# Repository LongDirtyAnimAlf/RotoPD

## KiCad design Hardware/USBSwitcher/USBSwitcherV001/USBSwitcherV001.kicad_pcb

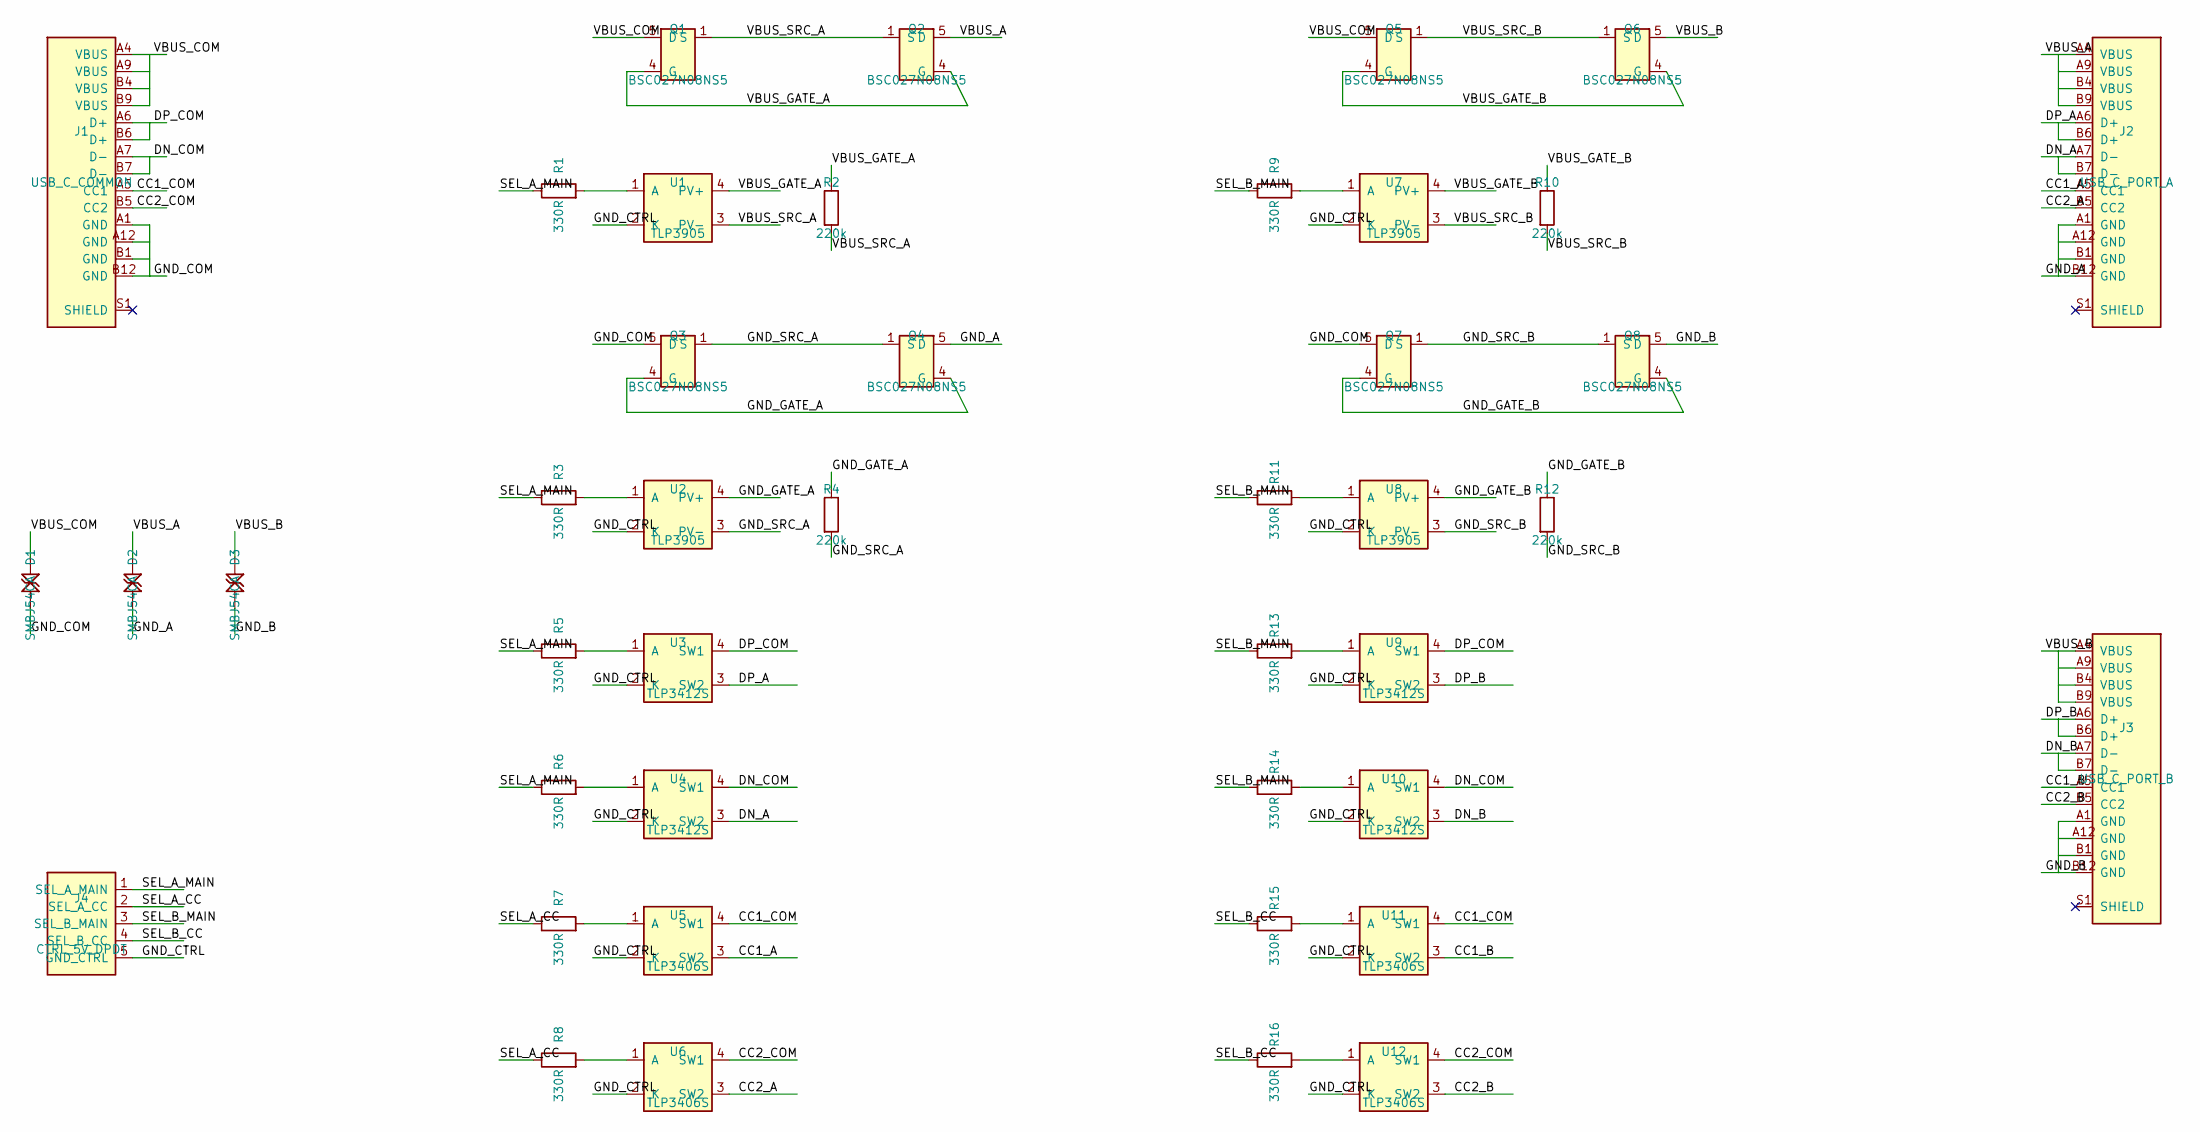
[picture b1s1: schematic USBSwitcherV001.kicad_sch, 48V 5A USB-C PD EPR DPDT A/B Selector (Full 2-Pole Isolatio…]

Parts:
D1, D2, D3: SMBJ54CA; D_SMB
J1: USB_C_COMMON; USB_C_Receptacle_GCT_USB4105-xx-A_16P_TopMnt_Horizontal
J2: USB_C_PORT_A; USB_C_Receptacle_GCT_USB4105-xx-A_16P_TopMnt_Horizontal
J3: USB_C_PORT_B; USB_C_Receptacle_GCT_USB4105-xx-A_16P_TopMnt_Horizontal
J4: CTRL_5V_DPDT; PinHeader_1x05_P2.54mm_Vertical
Q1, Q2, Q3, Q4, Q5, Q6, Q7, Q8: BSC027N08NS5; TDSON-8-1
R1, R3, R5, R6, R7, R8, R9, R11, R13, R14, R15, R16: 330R; R_0603_1608Metric
R2, R4, R10, R12: 220k; R_0603_1608Metric
U1, U2, U7, U8: TLP3905; SSOP-4_4.4x2.6mm_P1.27mm
U3, U4, U9, U10: TLP3412S; SSOP-4_4.4x2.6mm_P1.27mm
U5, U6, U11, U12: TLP3406S; SSOP-4_4.4x2.6mm_P1.27mm

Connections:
/CC1_A: J2.A5 (CC1), U5.3 (SW2)
/CC1_B: J3.A5 (CC1), U11.3 (SW2)
/CC1_COM: J1.A5 (CC1), U5.4 (SW1), U11.4 (SW1)
/CC2_A: J2.B5 (CC2), U6.3 (SW2)
/CC2_B: J3.B5 (CC2), U12.3 (SW2)
/CC2_COM: J1.B5 (CC2), U6.4 (SW1), U12.4 (SW1)
/DN_A: J2.A7 (D-), J2.B7 (D-), U4.3 (SW2)
/DN_B: J3.A7 (D-), J3.B7 (D-), U10.3 (SW2)
/DN_COM: J1.A7 (D-), J1.B7 (D-), U4.4 (SW1), U10.4 (SW1)
/DP_A: J2.A6 (D+), J2.B6 (D+), U3.3 (SW2)
/DP_B: J3.A6 (D+), J3.B6 (D+), U9.3 (SW2)
/DP_COM: J1.A6 (D+), J1.B6 (D+), U3.4 (SW1), U9.4 (SW1)
/GND_A: D2.1 (A1), J2.A1 (GND), J2.B12 (GND), Q4.5 (D)
/GND_B: D3.1 (A1), J3.A1 (GND), J3.B12 (GND), Q8.5 (D)
/GND_COM: D1.1 (A1), J1.A1 (GND), J1.B12 (GND), Q3.5 (D), Q7.5 (D)
/GND_CTRL: J4.5 (GND_CTRL), U1.2 (K), U2.2 (K), U3.2 (K), U4.2 (K), U5.2 (K), U6.2 (K), U7.2 (K), U8.2 (K), U9.2 (K), U10.2 (K), U11.2 (K), U12.2 (K)
/GND_GATE_A: Q3.4 (G), Q4.4 (G), R4.1, U2.4 (PV+)
/GND_GATE_B: Q7.4 (G), Q8.4 (G), R12.1, U8.4 (PV+)
/GND_SRC_A: Q3.1 (S), Q4.1 (S), R4.2, U2.3 (PV-)
/GND_SRC_B: Q7.1 (S), Q8.1 (S), R12.2, U8.3 (PV-)
/SEL_A_CC: J4.2 (SEL_A_CC), R7.1, R8.1
/SEL_A_MAIN: J4.1 (SEL_A_MAIN), R1.1, R3.1, R5.1, R6.1
/SEL_B_CC: J4.4 (SEL_B_CC), R15.1, R16.1
/SEL_B_MAIN: J4.3 (SEL_B_MAIN), R9.1, R11.1, R13.1, R14.1
/VBUS_A: D2.2 (A2), J2.A4 (VBUS), J2.B9 (VBUS), Q2.5 (D)
/VBUS_B: D3.2 (A2), J3.A4 (VBUS), J3.B9 (VBUS), Q6.5 (D)
/VBUS_COM: D1.2 (A2), J1.A4 (VBUS), J1.B9 (VBUS), Q1.5 (D), Q5.5 (D)
/VBUS_GATE_A: Q1.4 (G), Q2.4 (G), R2.1, U1.4 (PV+)
/VBUS_GATE_B: Q5.4 (G), Q6.4 (G), R10.1, U7.4 (PV+)
/VBUS_SRC_A: Q1.1 (S), Q2.1 (S), R2.2, U1.3 (PV-)
/VBUS_SRC_B: Q5.1 (S), Q6.1 (S), R10.2, U7.3 (PV-)
unnamed: R1.2, U1.1 (A)
unnamed: R3.2, U2.1 (A)
unnamed: R5.2, U3.1 (A)
unnamed: R6.2, U4.1 (A)
unnamed: R7.2, U5.1 (A)
unnamed: R8.2, U6.1 (A)
unnamed: R9.2, U7.1 (A)
unnamed: R11.2, U8.1 (A)
unnamed: R13.2, U9.1 (A)
unnamed: R14.2, U10.1 (A)
unnamed: R15.2, U11.1 (A)
unnamed: R16.2, U12.1 (A)

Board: 2 copper layers, 43 parts (0 on the bottom side), 43 nets, no tracks yet.

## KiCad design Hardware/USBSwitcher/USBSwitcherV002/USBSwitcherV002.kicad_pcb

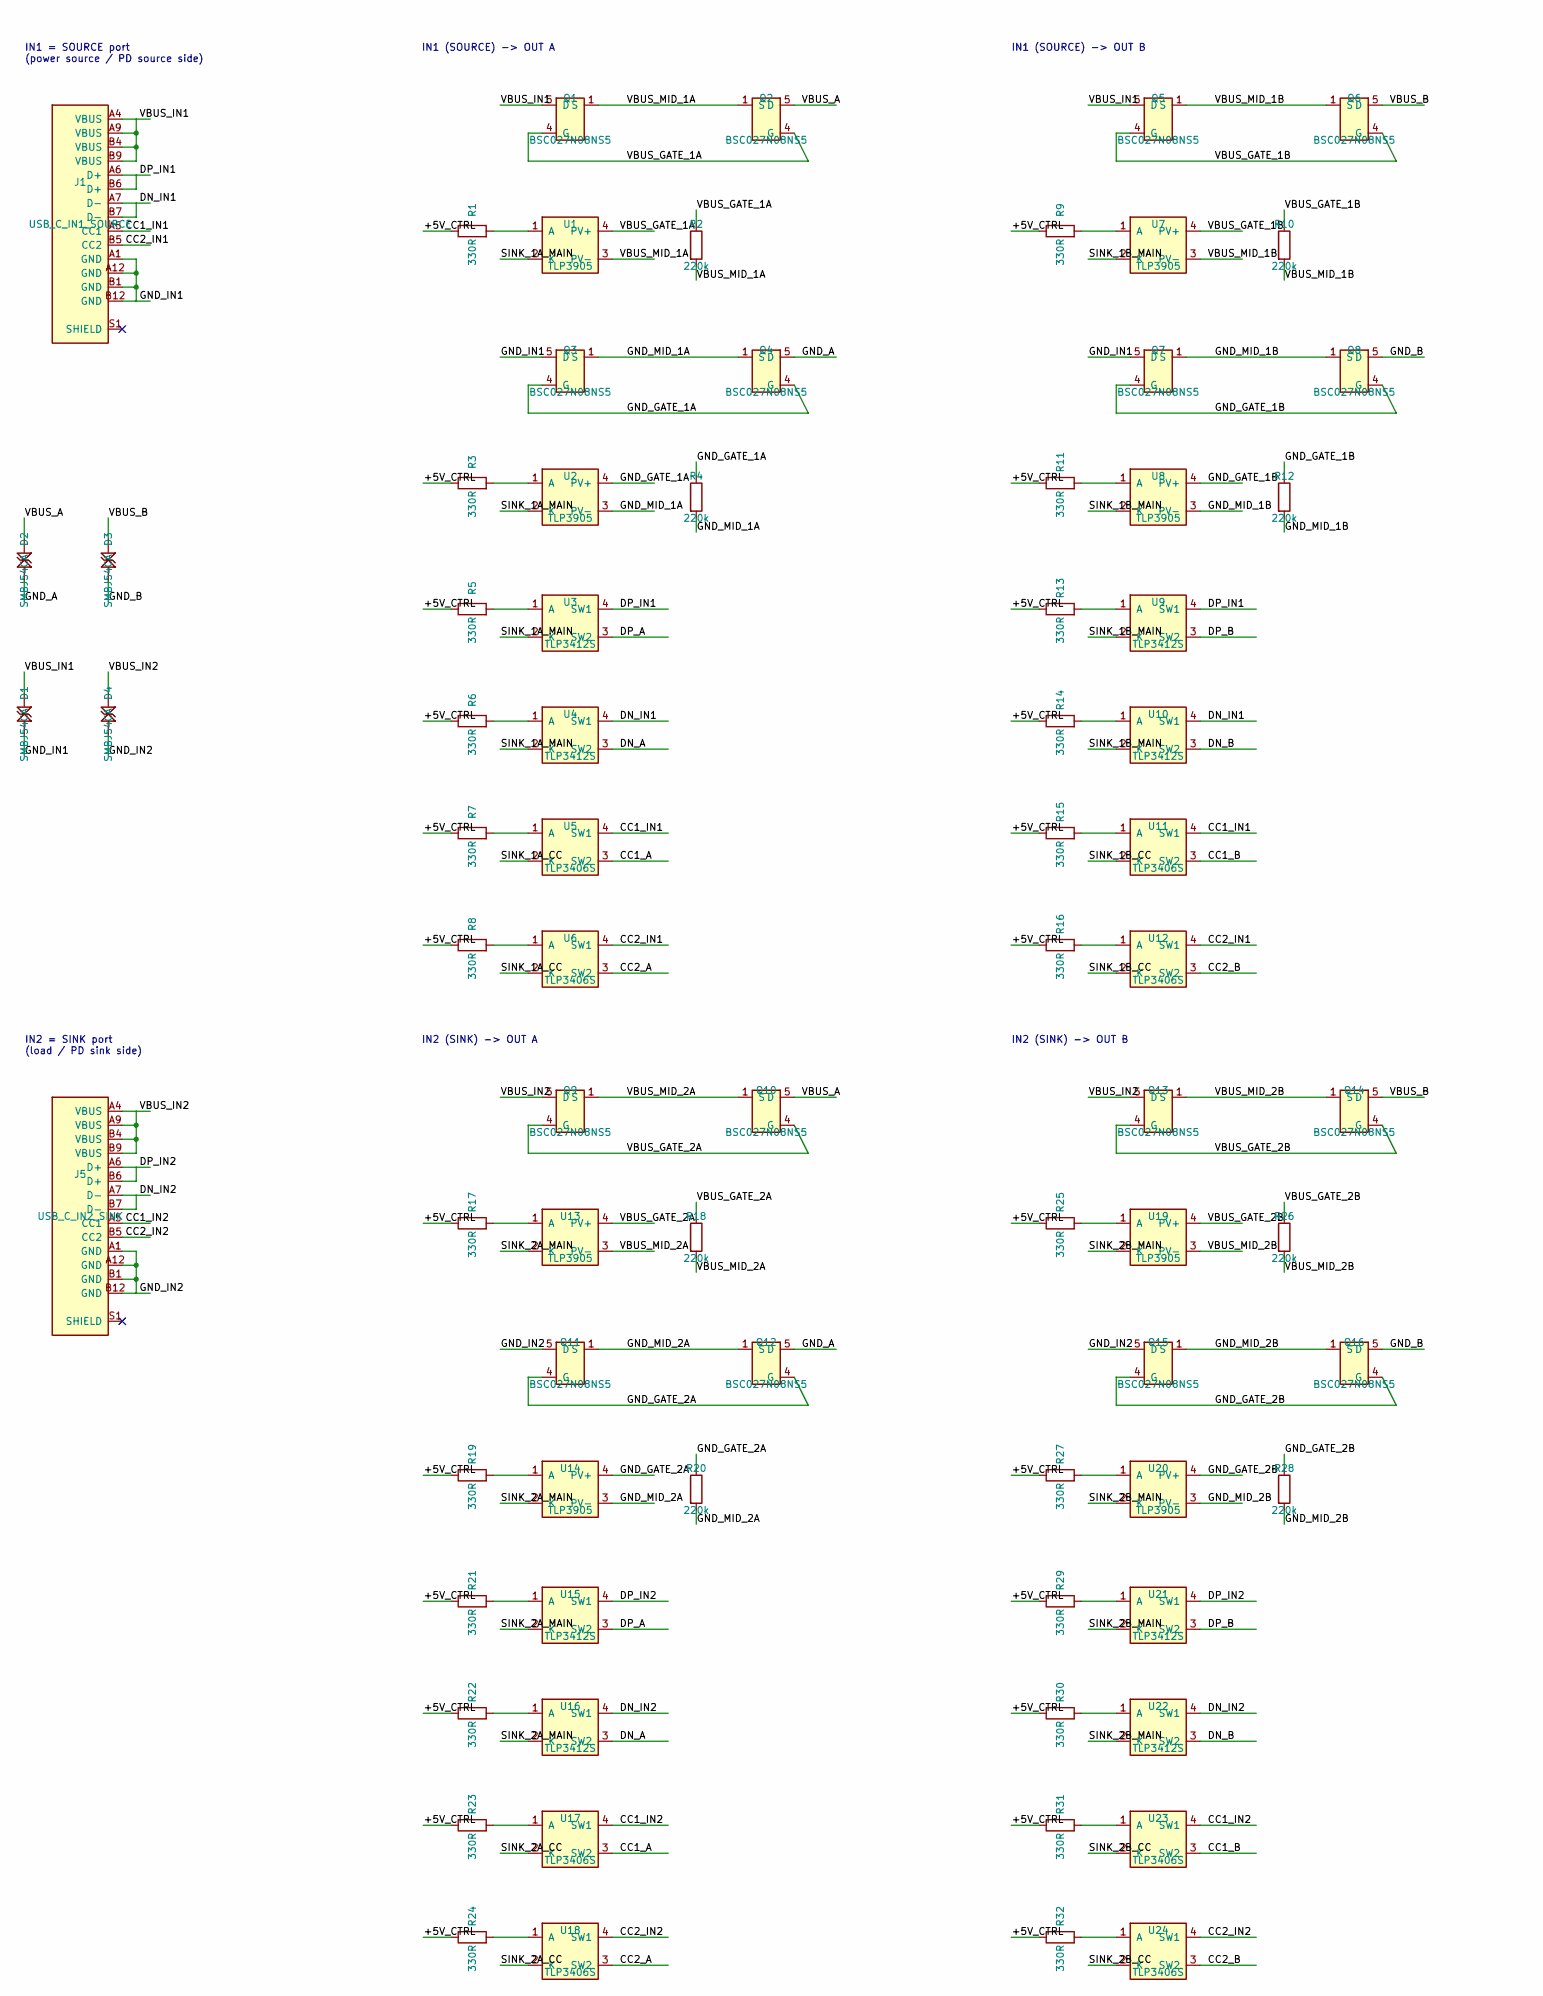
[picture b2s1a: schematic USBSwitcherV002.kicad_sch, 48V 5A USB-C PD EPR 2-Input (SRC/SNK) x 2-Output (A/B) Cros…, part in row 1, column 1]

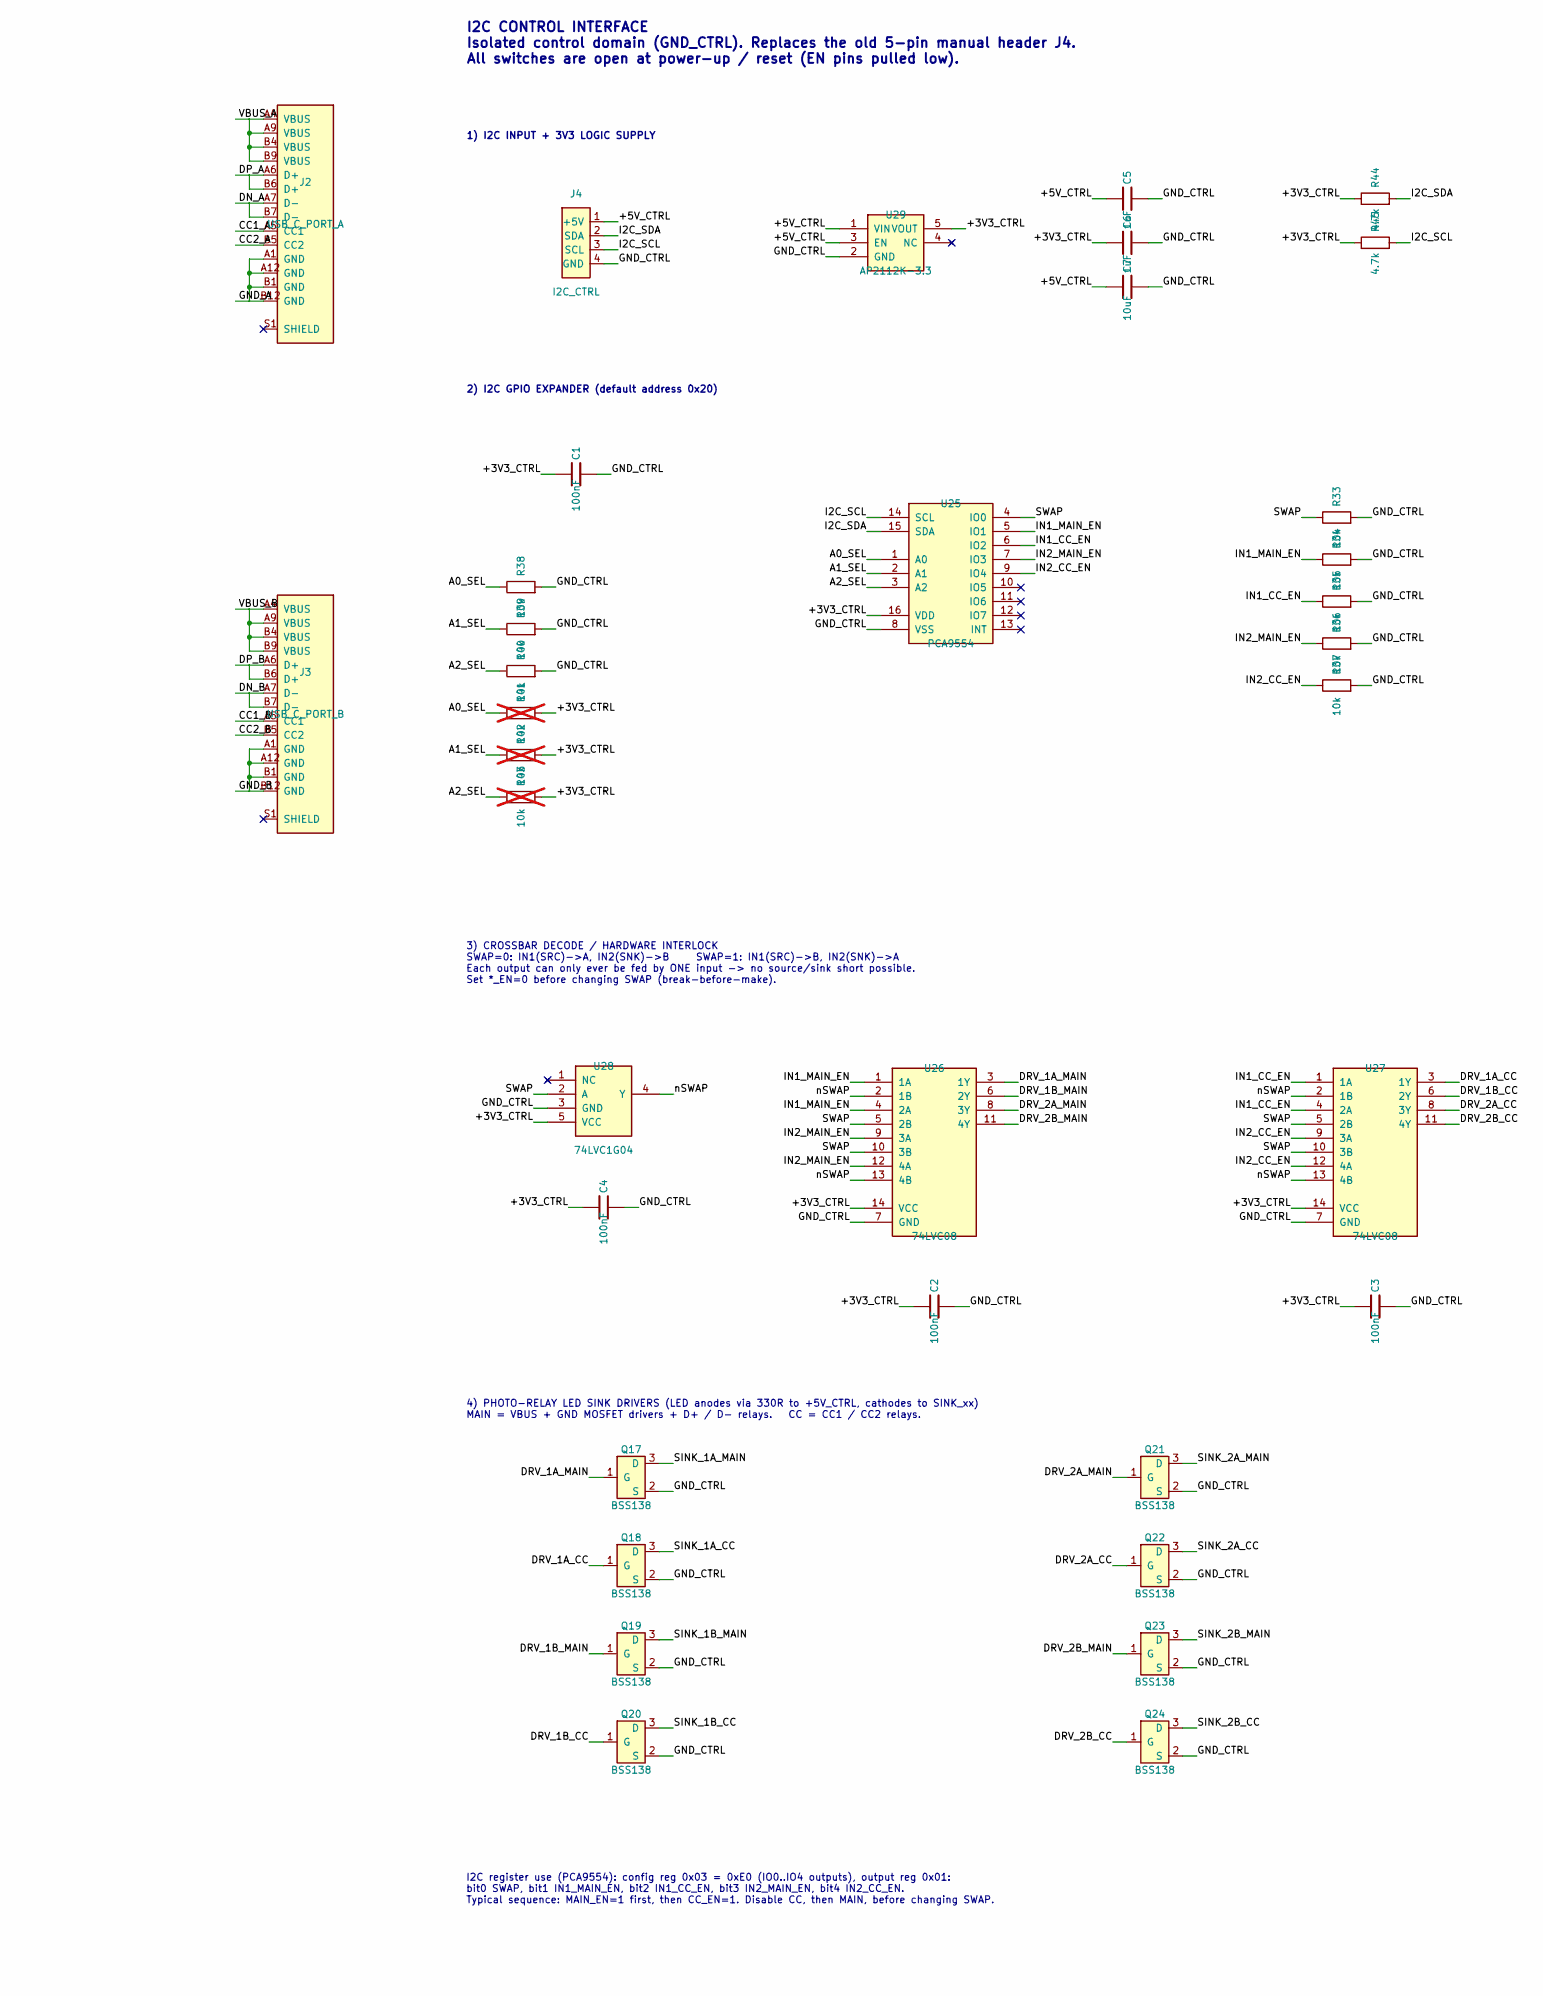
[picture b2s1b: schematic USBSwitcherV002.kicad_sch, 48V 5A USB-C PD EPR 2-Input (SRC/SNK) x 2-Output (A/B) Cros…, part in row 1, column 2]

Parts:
C1, C2, C3, C4: 100nF; C_0603_1608Metric
C5, C6: 1uF; C_0603_1608Metric
C7: 10uF; C_0805_2012Metric
D1, D2, D3, D4: SMBJ54CA; D_SMB
J1: USB_C_IN1_SOURCE; USB_C_Receptacle_GCT_USB4105-xx-A_16P_TopMnt_Horizontal
J2: USB_C_PORT_A; USB_C_Receptacle_GCT_USB4105-xx-A_16P_TopMnt_Horizontal
J3: USB_C_PORT_B; USB_C_Receptacle_GCT_USB4105-xx-A_16P_TopMnt_Horizontal
J4: I2C_CTRL; PinHeader_1x04_P2.54mm_Vertical
J5: USB_C_IN2_SINK; USB_C_Receptacle_GCT_USB4105-xx-A_16P_TopMnt_Horizontal
Q1, Q2, Q3, Q4, Q5, Q6, Q7, Q8, Q9, Q10, Q11, Q12, Q13, Q14, Q15, Q16: BSC027N08NS5; TDSON-8-1
Q17, Q18, Q19, Q20, Q21, Q22, Q23, Q24: BSS138; SOT-23
R1, R3, R5, R6, R7, R8, R9, R11, R13, R14, R15, R16, R17, R19, R21, R22, R23, R24, R25, R27, R29, R30, R31, R32: 330R; R_0603_1608Metric
R2, R4, R10, R12, R18, R20, R26, R28: 220k; R_0603_1608Metric
R33, R34, R35, R36, R37, R38, R39, R40: 10k; R_0603_1608Metric
R41, R42, R43: 10k; R_0603_1608Metric; not fitted
R44, R45: 4.7k; R_0603_1608Metric
U1, U2, U7, U8, U13, U14, U19, U20: TLP3905; SSOP-4_4.4x2.6mm_P1.27mm
U3, U4, U9, U10, U15, U16, U21, U22: TLP3412S; SSOP-4_4.4x2.6mm_P1.27mm
U5, U6, U11, U12, U17, U18, U23, U24: TLP3406S; SSOP-4_4.4x2.6mm_P1.27mm
U25: PCA9554; TSSOP-16_4.4x5mm_P0.65mm
U26, U27: 74LVC08; SOIC-14_3.9x8.7mm_P1.27mm
U28: 74LVC1G04; SOT-23-5
U29: AP2112K-3.3; SOT-23-5

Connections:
/+3V3_CTRL: C1.1, C2.1, C3.1, C4.1, C6.1, R41.2, R42.2, R43.2, R44.1, R45.1, U25.16 (VDD), U26.14 (VCC), U27.14 (VCC), U28.5 (VCC), U29.5 (VOUT)
/+5V_CTRL: C5.1, C7.1, J4.1 (+5V), R1.1, R3.1, R5.1, R6.1, R7.1, R8.1, R9.1, R11.1, R13.1, R14.1, R15.1, R16.1, R17.1, R19.1, R21.1, R22.1, R23.1, R24.1, R25.1, R27.1, R29.1, R30.1, R31.1, R32.1, U29.1 (VIN), U29.3 (EN)
/A0_SEL: R38.1, R41.1, U25.1 (A0)
/A1_SEL: R39.1, R42.1, U25.2 (A1)
/A2_SEL: R40.1, R43.1, U25.3 (A2)
/CC1_A: J2.A5 (CC1), U5.3 (SW2), U17.3 (SW2)
/CC1_B: J3.A5 (CC1), U11.3 (SW2), U23.3 (SW2)
/CC1_IN1: J1.A5 (CC1), U5.4 (SW1), U11.4 (SW1)
/CC1_IN2: J5.A5 (CC1), U17.4 (SW1), U23.4 (SW1)
/CC2_A: J2.B5 (CC2), U6.3 (SW2), U18.3 (SW2)
/CC2_B: J3.B5 (CC2), U12.3 (SW2), U24.3 (SW2)
/CC2_IN1: J1.B5 (CC2), U6.4 (SW1), U12.4 (SW1)
/CC2_IN2: J5.B5 (CC2), U18.4 (SW1), U24.4 (SW1)
/DN_A: J2.A7 (D-), J2.B7 (D-), U4.3 (SW2), U16.3 (SW2)
/DN_B: J3.A7 (D-), J3.B7 (D-), U10.3 (SW2), U22.3 (SW2)
/DN_IN1: J1.A7 (D-), J1.B7 (D-), U4.4 (SW1), U10.4 (SW1)
/DN_IN2: J5.A7 (D-), J5.B7 (D-), U16.4 (SW1), U22.4 (SW1)
/DP_A: J2.A6 (D+), J2.B6 (D+), U3.3 (SW2), U15.3 (SW2)
/DP_B: J3.A6 (D+), J3.B6 (D+), U9.3 (SW2), U21.3 (SW2)
/DP_IN1: J1.A6 (D+), J1.B6 (D+), U3.4 (SW1), U9.4 (SW1)
/DP_IN2: J5.A6 (D+), J5.B6 (D+), U15.4 (SW1), U21.4 (SW1)
/DRV_1A_CC: Q18.1 (G), U27.3 (1Y)
/DRV_1A_MAIN: Q17.1 (G), U26.3 (1Y)
/DRV_1B_CC: Q20.1 (G), U27.6 (2Y)
/DRV_1B_MAIN: Q19.1 (G), U26.6 (2Y)
/DRV_2A_CC: Q22.1 (G), U27.8 (3Y)
/DRV_2A_MAIN: Q21.1 (G), U26.8 (3Y)
/DRV_2B_CC: Q24.1 (G), U27.11 (4Y)
/DRV_2B_MAIN: Q23.1 (G), U26.11 (4Y)
/GND_A: D2.1 (A1), J2.A1 (GND), J2.A12 (GND), J2.B1 (GND), J2.B12 (GND), Q4.5 (D), Q12.5 (D)
/GND_B: D3.1 (A1), J3.A1 (GND), J3.A12 (GND), J3.B1 (GND), J3.B12 (GND), Q8.5 (D), Q16.5 (D)
/GND_CTRL: C1.2, C2.2, C3.2, C4.2, C5.2, C6.2, C7.2, J4.4 (GND), Q17.2 (S), Q18.2 (S), Q19.2 (S), Q20.2 (S), Q21.2 (S), Q22.2 (S), Q23.2 (S), Q24.2 (S), R33.2, R34.2, R35.2, R36.2, R37.2, R38.2, R39.2, R40.2, U25.8 (VSS), U26.7 (GND), U27.7 (GND), U28.3 (GND), U29.2 (GND)
/GND_GATE_1A: Q3.4 (G), Q4.4 (G), R4.1, U2.4 (PV+)
/GND_GATE_1B: Q7.4 (G), Q8.4 (G), R12.1, U8.4 (PV+)
/GND_GATE_2A: Q11.4 (G), Q12.4 (G), R20.1, U14.4 (PV+)
/GND_GATE_2B: Q15.4 (G), Q16.4 (G), R28.1, U20.4 (PV+)
/GND_IN1: D1.1 (A1), J1.A1 (GND), J1.A12 (GND), J1.B1 (GND), J1.B12 (GND), Q3.5 (D), Q7.5 (D)
/GND_IN2: D4.1 (A1), J5.A1 (GND), J5.A12 (GND), J5.B1 (GND), J5.B12 (GND), Q11.5 (D), Q15.5 (D)
/GND_MID_1A: Q3.1 (S), Q4.1 (S), R4.2, U2.3 (PV-)
/GND_MID_1B: Q7.1 (S), Q8.1 (S), R12.2, U8.3 (PV-)
/GND_MID_2A: Q11.1 (S), Q12.1 (S), R20.2, U14.3 (PV-)
/GND_MID_2B: Q15.1 (S), Q16.1 (S), R28.2, U20.3 (PV-)
/I2C_SCL: J4.3 (SCL), R45.2, U25.14 (SCL)
/I2C_SDA: J4.2 (SDA), R44.2, U25.15 (SDA)
/IN1_CC_EN: R35.1, U25.6 (IO2), U27.1 (1A), U27.4 (2A)
/IN1_MAIN_EN: R34.1, U25.5 (IO1), U26.1 (1A), U26.4 (2A)
/IN2_CC_EN: R37.1, U25.9 (IO4), U27.9 (3A), U27.12 (4A)
/IN2_MAIN_EN: R36.1, U25.7 (IO3), U26.9 (3A), U26.12 (4A)
/SINK_1A_CC: Q18.3 (D), U5.2 (K), U6.2 (K)
/SINK_1A_MAIN: Q17.3 (D), U1.2 (K), U2.2 (K), U3.2 (K), U4.2 (K)
/SINK_1B_CC: Q20.3 (D), U11.2 (K), U12.2 (K)
/SINK_1B_MAIN: Q19.3 (D), U7.2 (K), U8.2 (K), U9.2 (K), U10.2 (K)
/SINK_2A_CC: Q22.3 (D), U17.2 (K), U18.2 (K)
/SINK_2A_MAIN: Q21.3 (D), U13.2 (K), U14.2 (K), U15.2 (K), U16.2 (K)
/SINK_2B_CC: Q24.3 (D), U23.2 (K), U24.2 (K)
/SINK_2B_MAIN: Q23.3 (D), U19.2 (K), U20.2 (K), U21.2 (K), U22.2 (K)
/SWAP: R33.1, U25.4 (IO0), U26.5 (2B), U26.10 (3B), U27.5 (2B), U27.10 (3B), U28.2 (A)
/VBUS_A: D2.2 (A2), J2.A4 (VBUS), J2.A9 (VBUS), J2.B4 (VBUS), J2.B9 (VBUS), Q2.5 (D), Q10.5 (D)
/VBUS_B: D3.2 (A2), J3.A4 (VBUS), J3.A9 (VBUS), J3.B4 (VBUS), J3.B9 (VBUS), Q6.5 (D), Q14.5 (D)
/VBUS_GATE_1A: Q1.4 (G), Q2.4 (G), R2.1, U1.4 (PV+)
/VBUS_GATE_1B: Q5.4 (G), Q6.4 (G), R10.1, U7.4 (PV+)
/VBUS_GATE_2A: Q9.4 (G), Q10.4 (G), R18.1, U13.4 (PV+)
/VBUS_GATE_2B: Q13.4 (G), Q14.4 (G), R26.1, U19.4 (PV+)
/VBUS_IN1: D1.2 (A2), J1.A4 (VBUS), J1.A9 (VBUS), J1.B4 (VBUS), J1.B9 (VBUS), Q1.5 (D), Q5.5 (D)
/VBUS_IN2: D4.2 (A2), J5.A4 (VBUS), J5.A9 (VBUS), J5.B4 (VBUS), J5.B9 (VBUS), Q9.5 (D), Q13.5 (D)
/VBUS_MID_1A: Q1.1 (S), Q2.1 (S), R2.2, U1.3 (PV-)
/VBUS_MID_1B: Q5.1 (S), Q6.1 (S), R10.2, U7.3 (PV-)
/VBUS_MID_2A: Q9.1 (S), Q10.1 (S), R18.2, U13.3 (PV-)
/VBUS_MID_2B: Q13.1 (S), Q14.1 (S), R26.2, U19.3 (PV-)
/nSWAP: U26.2 (1B), U26.13 (4B), U27.2 (1B), U27.13 (4B), U28.4 (Y)
unnamed: R1.2, U1.1 (A)
unnamed: R3.2, U2.1 (A)
unnamed: R5.2, U3.1 (A)
unnamed: R6.2, U4.1 (A)
unnamed: R7.2, U5.1 (A)
unnamed: R8.2, U6.1 (A)
unnamed: R9.2, U7.1 (A)
unnamed: R11.2, U8.1 (A)
unnamed: R13.2, U9.1 (A)
unnamed: R14.2, U10.1 (A)
unnamed: R15.2, U11.1 (A)
unnamed: R16.2, U12.1 (A)
unnamed: R17.2, U13.1 (A)
unnamed: R19.2, U14.1 (A)
unnamed: R21.2, U15.1 (A)
unnamed: R22.2, U16.1 (A)
unnamed: R23.2, U17.1 (A)
unnamed: R24.2, U18.1 (A)
unnamed: R25.2, U19.1 (A)
unnamed: R27.2, U20.1 (A)
unnamed: R29.2, U21.1 (A)
unnamed: R30.2, U22.1 (A)
unnamed: R31.2, U23.1 (A)
unnamed: R32.2, U24.1 (A)

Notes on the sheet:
IN1 (SOURCE) -> OUT A
IN1 (SOURCE) -> OUT B
IN2 (SINK) -> OUT B
3) CROSSBAR DECODE / HARDWARE INTERLOCK SWAP=0: IN1(SRC)->A, IN2(SNK)->B SWAP=1: IN1(SRC)->B, IN2(SNK)->A Each output can only ever be fed by ONE input -> no source/sink short possible. Set *_EN=0 before changing SWAP (break-before-make).
1) I2C INPUT + 3V3 LOGIC SUPPLY
IN1 = SOURCE port (power source / PD source side)
I2C register use (PCA9554): config reg 0x03 = 0xE0 (IO0..IO4 outputs), output reg 0x01: bit0 SWAP, bit1 IN1_MAIN_EN, bit2 IN1_CC_EN, bit3 IN2_MAIN_EN, bit4 IN2_CC_EN. Typical sequence: MAIN_EN=1 first, then CC_EN=1. Disable CC, then MAIN, before changing SWAP.
I2C CONTROL INTERFACE Isolated control domain (GND_CTRL). Replaces the old 5-pin manual header J4. All switches are open at power-up / reset (EN pins pulled low).
4) PHOTO-RELAY LED SINK DRIVERS (LED anodes via 330R to +5V_CTRL, cathodes to SINK_xx) MAIN = VBUS + GND MOSFET drivers + D+ / D- relays. CC = CC1 / CC2 relays.
2) I2C GPIO EXPANDER (default address 0x20)
IN2 (SINK) -> OUT A
IN2 = SINK port (load / PD sink side)

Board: 2 copper layers, 114 parts (0 on the bottom side), 94 nets, no tracks yet.
